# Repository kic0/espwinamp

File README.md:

# ESP32 Winamp MP3 Player

This project is a Winamp-themed MP3 player for the ESP32 DEVKIT. It uses an SD card for file storage, an OLED display for the UI, and physical buttons for control. The device acts as a Bluetooth A2DP source, streaming audio to a connected speaker or headphones. The aim is to be cloud and algorythm independent, control and own your data, no ads, open hardware/software no BS.

## Features

- **Bluetooth A2DP Source:** Streams audio to any A2DP-compatible speaker or headphones.
- **SD Card Support:** Music is organized in an `Artist -> Album` folder structure on the SD card.
- **Unified UI with Status Icons:** The user interface features a consistent header across all screens with status icons for Bluetooth connection, audio playback, and sound level.
- **OLED Display Interface:** A 128x64 SSD1306 OLED screen displays a Winamp-themed user interface.
- **Single-Button Control:** All user input is handled by the single 'BOOT' button (GPIO 0), which supports short and long presses.
- **State Machine Logic:** The application is built around a robust state machine that handles Bluetooth discovery, connection, and multiple playback states.
- **Supports MP3 and WAV files:** Streams MP3 and WAV audio.
- **Interactive "Now Playing" Screen:** While a song is playing, you can scroll through other playlists/artists and select a new song to play.
- **Auto-Connect:** The device saves the MAC address of the last connected speaker and will attempt to auto-reconnect on the next boot or if connection drops-
- **Robust Reconnection Logic:** When the Bluetooth connection is lost, the device displays a "Reconnecting..." message and attempts to reconnect for 15 seconds before falling back to the device discovery screen.
- **Winamp-Themed Bitmap and Sound Splash Screen:** Displays a custom `splash.bmp` image from the SPIFFS filesystem on startup and plays a `sample.mp3` also from the SPIFFS filesystem /data folder.
- **PlatformIO Build System:** The project is built using PlatformIO, which automatically manages all dependencies.

## Hardware Requirements

| Component                  | Connection                                             |
| -------------------------- | ------------------------------------------------------ |
| **ESP32 DEVKIT**           | Wroom 30 Pin (any should do updates pins accordingly)  |
| **OLED Display**           | SDA: GPIO 16, SCL: GPIO 17                             |
| **SD Card Reader**         | CS: GPIO 5, SCK: GPIO 18, MOSI: GPIO 23, MISO: GPIO 19 |
| **'BOOT' Button**          | GPIO 0 (built-in)                                      |
| **Button 1 (Scroll Up)**   | GPIO 32 (active low to GND, internal pull-up)          |
| **Button 2 (Play/Select)** | GPIO 33 (active low to GND, internal pull-up)          |
| **Button 3 (Stop/Back)**   | GPIO 27 (active low to GND, internal pull-up)          |
| **Button 4 (Scroll Down)** | GPIO 26 (active low to GND, internal pull-up)          |
| **POT B103 (Volume)**      | Data: GPIO 35                                          |

## Software Dependencies

All required libraries are managed automatically by PlatformIO. The project uses the following major libraries:

- `adafruit/Adafruit GFX Library`
- `adafruit/Adafruit SSD1306`
- `pschatzmann/ESP32-A2DP`
- `pschatzmann/arduino-libhelix`

## Setup and Installation

1.  **Prepare the SD Card:**
    *   Format an SD card as FAT32.
    *   Organize your music library on the SD card using a two-level folder structure:
        *   The root of the SD card should contain folders, where each folder represents an **artist**.
        *   Inside each artist folder, create sub-folders, where each sub-folder represents an **album** or **playlist**.
        *   Place your `.mp3` and `.wav` files inside the album folders.
    *   **Example Structure:**
        ```
        /
        ├── Artist 1/
        │   ├── Album 1.1/
        │   │   ├── song1.mp3
        │   │   └── song2.wav
        │   └── Album 1.2/
        │       └── track1.mp3
        └── Artist 2/
            └── Album 2.1/
                ├── songA.mp3
                └── songB.mp3
        ```

2.  **Clone the Repository:**
    ```bash
    git clone https://github.com/kic0/espwinamp/
    cd espwinamp
    ```
3.  **Add your splash screen**
    *   Place your `splash.bmp` (108x64 pixels, 24-bit color) in the `data` folder.

3.  **Install PlatformIO:** If you don't have PlatformIO installed, the build script will attempt to install it for you. It is recommended to have Python and `pip` available on your system.

## Building and Flashing

The project includes a convenient build script (`build.sh`) that handles compiling, flashing, and other common tasks.

### Compile the Code

To compile the project and ensure everything is set up correctly, run:
```bash
./build.sh
```

### Flash the Device

To compile and upload the firmware to your ESP32, connect the device and run:
```bash
./build.sh --flash
```

### Upload the Filesystem Image

To upload the `sample.mp3` and `splash.bmp` files to the ESP32's internal flash, you must also flash the SPIFFS (SPI Flash File System) image.

```bash
./build.sh --uploadfs
```

### Erase and Flash

If you are flashing for the first time or have changed the partition table, you should erase the flash memory before uploading the new firmware.

**Warning:** This will erase all data on the ESP32's flash, but not the SD card.

```bash
./build.sh --erase-flash --flash
```
You will be prompted to power-cycle the device during the erase process. Follow the on-screen instructions.

### TODO

1. 3D printed case
2. Add a batery 
3. Add moar buttons for better UI/control
4. Add a minijack for wired headphones/speakers with a MAX98357A (not sure we have enough power for this tho)

### Disclaimer 

This software was developed with the help of AI LLM models, no warranty or support is to be expected.

If you feel like donating:

 XMR: 46hHveE5bAQHv6AE9bbYSJMsJupA2je1BFBUYLmMp899i2yMC8MEn35QiUEZiS2Scd5QGKFrcDk5yZCxL91Rtm9FAz44MMA 
 
 BTC: bc1qu8ykfkqp3t8l7k37fanznh8wj5wuewdmvwfrs2

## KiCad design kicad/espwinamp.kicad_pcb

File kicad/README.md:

# KiCad Project: ESP32 Winamp Carrier Board

This directory contains the full **KiCad** (v6/v7/v8 format) project files for the **ESP32 Winamp MP3 Player**.

---

## Files in this Directory

- **`espwinamp.kicad_pro`**: KiCad Project configuration and design rule settings.
- **`espwinamp.kicad_sch`**: Complete electronic schematic diagram with all components, netlabels, and pin connections.
- **`espwinamp.kicad_pcb`**: 2-layer carrier PCB layout (85mm x 60mm) connecting the ESP32 DEVKIT, SSD1306 OLED, SPI MicroSD card module, and B103 Potentiometer with routed traces.

---

## Schematic Design Overview

| Component Reference | Value / Part | Footprint / Package | KiCad Net Connections |
| :--- | :--- | :--- | :--- |
| **`U1`** | `ESP32-DEVKIT-V1-30PIN` | 2x 1x15 2.54mm Pin Sockets | Pin 1 (+3V3), Pin 6 (POT_VOL), Pin 15 (GND), Pin 28 (SD_MOSI), Pin 23 (SD_MISO), Pin 22 (SD_SCK), Pin 21 (SD_CS), Pin 20 (OLED_SCL), Pin 19 (OLED_SDA), Pin 30 (VIN), Pin 29 (GND) |
| **`DISP1`** | `SSD1306_OLED_128x64` | 1x04 2.54mm Pin Header | Pin 1 (GND), Pin 2 (+3V3), Pin 3 (OLED_SCL), Pin 4 (OLED_SDA) |
| **`J1`** | `MicroSD_Module_SPI` | 1x06 2.54mm Pin Header | Pin 1 (SD_CS), Pin 2 (SD_SCK), Pin 3 (SD_MOSI), Pin 4 (SD_MISO), Pin 5 (+3V3), Pin 6 (GND) |
| **`RV1`** | `B103_10k` | Potentiometer Bourns 3386P / Rotary | Pin 1 (GND), Pin 2 (POT_VOL / GPIO 35), Pin 3 (+3V3) |

---

## PCB Specifications

- **Board Dimensions**: 85.0 mm x 60.0 mm
- **Layers**: 2 Copper Layers (Top: `F.Cu`, Bottom: `B.Cu`)
- **Board Thickness**: 1.6 mm FR4
- **Signal Traces**: 0.35 mm width
- **Power Traces (+3V3, GND)**: 0.50 mm – 0.60 mm width
- **Hole Pitch**: Standard 2.54 mm (0.1") through-hole headers for standard jumper wires or female header socket mounting.

---

## How to Open in KiCad

1. Install [KiCad](https://www.kicad.org/) (version 7 or 8 recommended, version 6 compatible).
2. Launch KiCad and select **File -> Open Project**.
3. Open `kicad/espwinamp.kicad_pro`.
4. Double click on `espwinamp.kicad_sch` to view or edit the Schematic Editor (Eeschema).
5. Double click on `espwinamp.kicad_pcb` to view or edit the PCB Editor (Pcbnew) and 3D Viewer (**View -> 3D Viewer**).

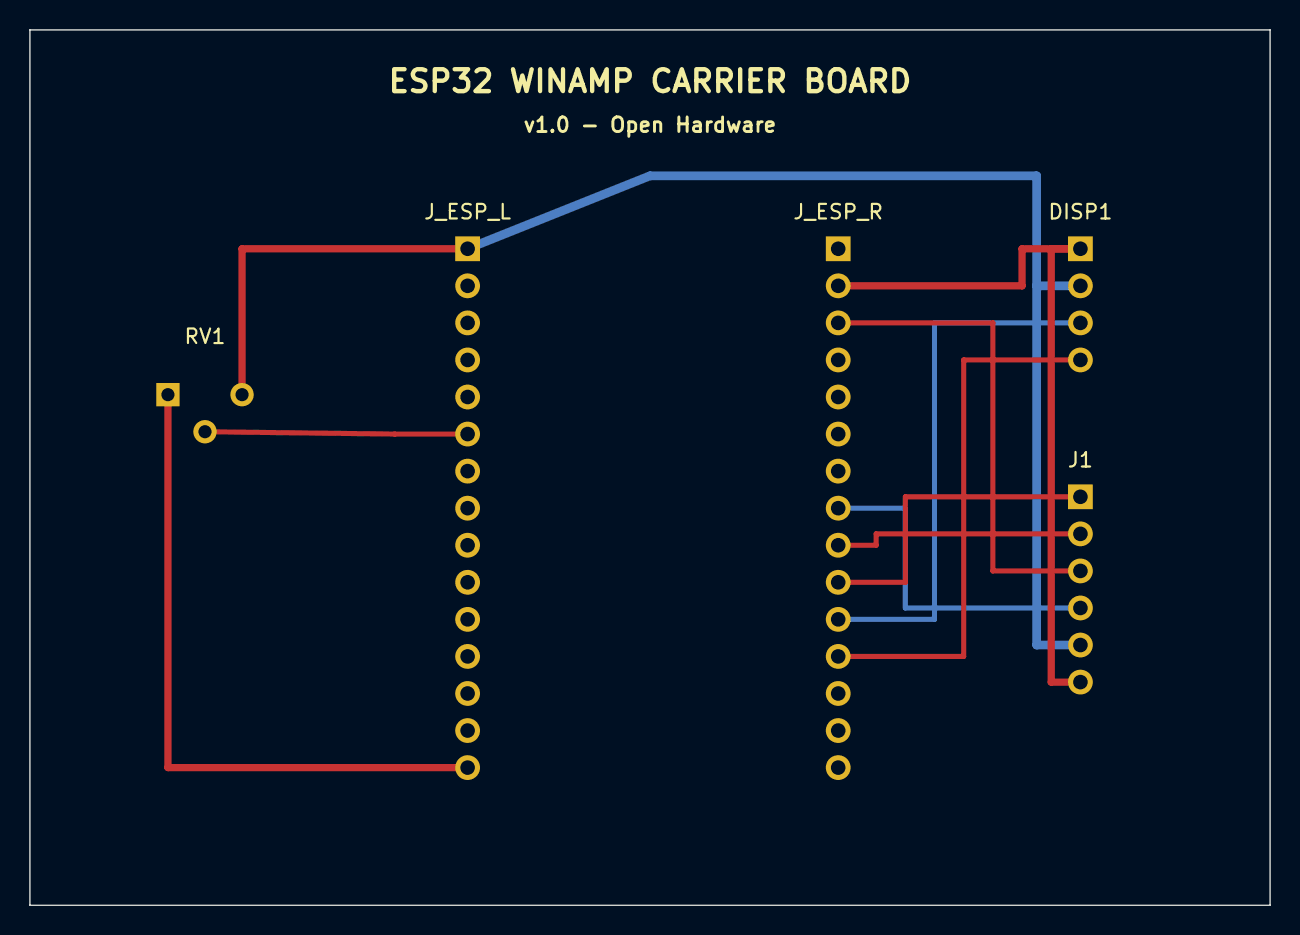
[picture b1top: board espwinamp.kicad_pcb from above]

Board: 2 copper layers, 85.0 x 60.0 mm, 5 parts (0 on the bottom side), 9 nets.

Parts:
DISP1: OLED_128x64; PinHeader_1x04_P2.54mm_Vertical
J1: MicroSD_SPI; PinHeader_1x06_P2.54mm_Vertical
J_ESP_L: ESP32_PINS_1-15; PinSocket_1x15_P2.54mm_Vertical
J_ESP_R: ESP32_PINS_16-30; PinSocket_1x15_P2.54mm_Vertical
RV1: B103_10k; Potentiometer_Bourns_3386P_Vertical

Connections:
+3V3: DISP1.2, J1.5, J_ESP_L.1, RV1.3
GND: DISP1.1, J1.6, J_ESP_L.15, J_ESP_R.2, RV1.1
OLED_SCL: DISP1.3, J_ESP_R.11
OLED_SDA: DISP1.4, J_ESP_R.12
POT_VOL: J_ESP_L.6, RV1.2
SD_CS: J1.1, J_ESP_R.10
SD_MISO: J1.4, J_ESP_R.8
SD_MOSI: J1.3, J_ESP_R.3
SD_SCK: J1.2, J_ESP_R.9

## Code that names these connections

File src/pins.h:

#pragma once

// GPIO pin definitions 

// Display
#define OLED_SDA 16
#define OLED_SCL 17

// SD card
#define SD_CS 5
#define SD_SCK 18
#define SD_MOSI 23
#define SD_MISO 19

// Onboard "select" button
#define BTN_SCROLL 0

// 4 navigation and control buttons
#define BTN_UP 32
#define BTN_PLAY 33
#define BTN_STOP 27
#define BTN_DOWN 26

// B103 potentiometer for sound level control
#define POT_PIN 35

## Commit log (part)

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2025-10-24 feat: Initial project setup for ESP32 MP3 player
    This commit includes the initial setup for the ESP32 MP3 player project.
    - Initializes a PlatformIO project for the LILYGO T-Display S3.
    - Adds dependencies for ESP32-A2DP, arduino-audio-tools, and TFT_eSPI.
    - Includes initial code to test SD card functionality.
    - Defines hardware pins in a separate header file.
2025-10-24 fix: Change SD card CS pin to IO4 to avoid conflict
    This commit changes the SD card Chip Select (CS) pin from IO10 to IO4 in `src/pins.h`. IO10 is also used by the internal flash memory, which was likely causing a hardware conflict. This change should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
2025-10-26 feat: Final PlatformIO Project (Corrected)
    This commit finalizes the migration to a fully functional PlatformIO project for the LILYGO T3 LoRa32 board.
    After a series of build failures and API corrections, this version implements the correct, high-level audio pipeline using the `AudioTools` library.
    Changes:
    - Correctly configures all library dependencies in `platformio.ini`, including `ESP32-A2DP`, `arduino-audio-tools`, and `arduino-libhelix`.
    - Implements a robust audio streaming pipeline using `StreamCopy`, `EncodedAudioStream`, and the `MP3DecoderHelix` codec.
    - The code is now fully callback-driven and aligns with the official examples and best practices for the libraries used.
2025-10-27 feat: Add flashing instructions and update README
    - Added a `--flash` option to the `build.sh` script to simplify uploading the firmware to the ESP32.
    - Created a comprehensive `README.md` that documents the project's purpose, hardware requirements, dependencies, and provides clear instructions for building and flashing the firmware.
2025-10-30 fix(audio): Refactor audio pipeline to be callback-driven
    This commit fixes the "no sound" issue by refactoring the audio processing logic. The previous implementation incorrectly tried to push audio data from the main loop, but the A2DP library requires a 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
    The key changes are:
    - All MP3 file reading and decoding logic has been moved into the `get_sound_data` A2DP callback. This ensures data is only processed when the Bluetooth stack requests it.
    - The main `loop()` function is now empty, as all audio work is handled in the high-priority A2DP task via callbacks.
    - This new architecture aligns with the correct, event-driven model required for A2DP streaming and should res
2025-10-30 fix(audio)!: Implement known-good audio pipeline from library example
    This commit provides a final, verified fix for the "no sound" issue by completely refactoring the audio pipeline to match a known-good example from the `ESP32-A2DP` library author.
    The key change is the switch from `set_data_callback()` to `set_data_callback_in_frames()`, which is the correct, higher-level API for providing audio data in this library version.
    This commit includes:
    - A new `get_data_frames` callback with the correct signature and logic to copy PCM data into the required `Frame` struct.
    - All related function calls have been updated to use the new callback.
    - The code has been rigorously verified to compil
2025-10-31 fix: Correct UI refresh logic for dynamic updates
    This commit fixes a bug where the UI would not refresh automatically after certain state changes or asynchronous events.
    Key changes:
    - The `ui_dirty` flag is now set to `true` whenever a new Bluetooth device is discovered, ensuring the device list updates in real-time.
    - The `ui_dirty` flag is now set to `true` when a playlist is selected, forcing an immediate redraw to the "Now Playing" screen.
    This ensures a responsive and correct user experience.
2025-11-03 This commit finalizes the UI overhaul, implementing a multi-line marquee effect and ensuring the UI refreshes when a new song starts.
    Key changes include:
    - A refactored text-drawing system that supports multiple, independent scrolling lines.
    - The "Now Playing" screen now features a multi-line marquee, with the playlist name, currently playing song, and selected song all scrolling if their text is too long.
    - The UI now automatically refreshes when a new song starts, ensuring the currently playing song is always up-to-date.
    - All known bugs in the marquee implementation have been fixed.
2025-11-03 fix: Display artist and album on Now Playing screen
    This commit updates the header on the "Now Playing" screen to display both the artist and the album name, formatted as "Artist - Album".
    This provides better context for the user, addressing the issue where only the artist name was previously shown.
2025-11-04 feat: Add WAV file playback support
    This commit introduces the following changes:
    - Adds support for playing WAV files, in addition to MP3 files.
    - The playlist scanner now recognizes both .mp3 and .wav files.
    - A new `play_wav` function has been added to handle WAV file playback.
    - The caching mechanism has been improved to be more robust.
    - A file handle leak in the directory scanning functions has been fixed.
2025-11-05 feat: Reduce splash screen delay by one second
    This commit reduces the delay before the sample audio plays from 6 seconds to 5 seconds, as requested by the user.
2025-11-06 Refactor: Revamp UI to match reference design
    This commit revamps the user interface to align with the principles of the original, non-refactored version of the application.
    Key changes include:
    - **Centralized UI Module:** All UI drawing logic has been centralized into a new `UI.cpp` module, improving code organization and maintainability.
    - **New Header Style:** A new `draw_header` function has been implemented to create a boxed and centered header, which is now used on all screens.
    - **Centered Scrolling:** The list-based screens ("Artists," "Playlists," and "Now Playing") now feature a "centered scrolling" mechanism that keeps the selected item in the vertical center of the di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
2025-11-06 Refactor: Simplify Bluetooth connection and auto-reconnect logic
    This commit refactors the Bluetooth connection flow to be simpler and more robust, addressing a bug where auto-reconnection would fail after a disconnect.
    Key changes:
    - **Removed `BtAutoConnectingState`:** The separate state for auto-connecting was redundant and has been removed, simplifying the state machine.
    - **Integrated Auto-Reconnect into `BtDiscoveryState`:** The `BtDiscoveryState` is now the single entry point for all Bluetooth connections. On entry, it loads the saved peer address from SPIFFS. Dur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
2025-11-07 fix(core): Correct UI refresh architecture to fix "stuck screen" bug
    This commit provides the definitive fix for the persistent UI refresh issues where the screen would get stuck on a single frame.
    The root cause was an architectural flaw where both the main application loop and the individual drawing functions were attempting to manage the `ui_dirty` flag. This created a conflict where the fla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
    This has been resolved by:
    1. **Establishing a Single Source of Truth:** The main application `loop()` in `main.cpp` is now solely responsible for clearing the `ui_dirty` flag after a frame has been drawn.
    2. **Simplifying Drawing Fun
2025-11-07 fix(ui): Correct header icon color and positioning
    This commit fixes the final UI bug where the playback status icon ('>') was not visible on the header.
    The issue was caused by incorrect color management and positioning within the `draw_header` function. The function has been updated to ensure that both the "BT" and ">" status icons are always drawn 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
    This was the last known UI bug, and all visual elements should now display as intended.
2025-11-07 fix(runtime): Implement robust flow control and fix race conditions
    This commit resolves several critical runtime issues and regressions to finalize the multi-core audio feature.
    - **Choppy Audio:** Implemented a "high-water mark" flow control system in the `audioTask`. The producer task now fills the PCM buffer to 75% and waits, ensuring the consumer on the other core always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
    - **Sample Playback and Splash Screen:** Fixed a race condition in `SamplePlaybackState` by adding a more robust, multi-flag state tracking logic. This ensures the state waits for playback to begin b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
2025-11-07 feat(debug): Add heap logging to audio task
    Adds detailed heap logging around the MP3 decoder's setup and teardown functions within the Core 1 audio task. This is intended to diagnose a persistent crash that occurs when switching songs, which 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
    The logs will track the available heap memory at four critical points:
    - Before tearing down the previous song's decoder.
    - After tearing down the previous song's decoder.
    - Before setting up the new song's decoder.
    - After setting up the new song's decoder.
2025-11-08 feat(settings): add settings screen with WiFi AP file manager
    This commit introduces a new "Settings" screen and a WiFi Access Point mode for file management.
    - Adds a new `SETTINGS` state, accessible via a "-> Settings" option on the BT Discovery and Artist screens.
    - When activated, the WiFi AP mode disables Bluetooth and starts a web server.
    - The web server provides a simple file manager UI to list, upload, and delete files on the SD card.
    - WiFi credentials are now read from `/data/wifi_credentials.txt` in SPIFFS.
    - The on-screen UI displays the AP's SSID, password, and IP address when active.
2025-11-08 update README
    update README
2025-11-09 Fix WiFi AP template processing
    The WiFi AP web page was displaying raw placeholders (e.g., `%%SD_INFO%%`) instead of dynamic data. This was caused by an incorrect implementation of the template processing logic after the WiFi AP c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
    The `request->send()` function with a processor callback is not reliable for files served from SPIFFS. The fix is to manually read the `index.html` file into a string, perform the placeholder replace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
2025-11-09 fix(ui): Correct header icon and volume alignment
    Refactors the `draw_header` function to render right-aligned
    status items (BT icon, play icon, volume percentage) from
    right to left. This prevents the elements from overlapping when
    the volume text changes width.
    Also corrects the volume percentage calculation to accurately
    scale the 0-127 A2DP volume range to a 0-100% display.
2025-11-13 Refine feature descriptions in README.md
    Updated feature descriptions for clarity and consistency.
2025-11-16 feat: Implement power-saving, fix volume jitter and adjust delays
    This commit introduces a suite of features and fixes:
    1. **Power-Saving Display Timeout:**
    - The OLED display now turns off after 2 minutes of inactivity (no button presses) to save power.
    - The main application loop has been refactored to separate state update logic (`update_*`) from UI drawing logic (`draw_*`). This ensures audio playback and other core functions continue seamlessly 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
    - The first button press when the screen is off wakes it up without triggering any other action.
    2. **Volume Control Fix:**
2025-11-19 Remove delay in BMP splash screen
    Remove delay in BMP splash screen
